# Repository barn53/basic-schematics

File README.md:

# basic-schematics

KiCAD dependencies:

https://github.com/gerdmuller/barn53-kicad-library.git

https://github.com/Digi-Key/digikey-kicad-library.git

KiCAD path:

```${BARN53_KICAD_DIR}```

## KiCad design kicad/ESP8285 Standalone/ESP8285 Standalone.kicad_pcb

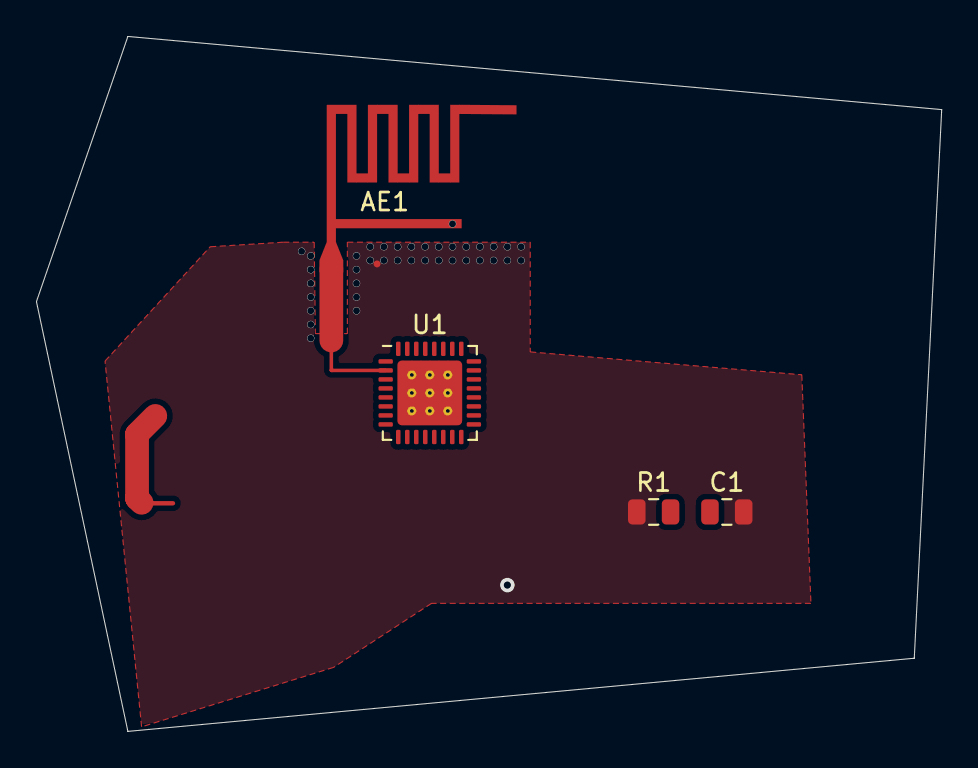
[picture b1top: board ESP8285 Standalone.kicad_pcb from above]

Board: 2 copper layers, 50.3 x 38.6 mm, 4 parts (0 on the bottom side), 2 nets.

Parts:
AE1: PCB_Antenna_2.4GHz_1mm; PCB_Antenna_2.4GHz_MIFA_Layout_1mm_FR4_PCB
C1: C; C_0805_2012Metric
R1: R; R_0805_2012Metric
U1: ESP_8285; QFN-32-1EP_5x5mm_P0.5mm_EP3.6x3.6mm_ThermalVias

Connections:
GND: AE1.2, C1.2, R1.1, U1.33
unnamed: AE1.1, U1.2

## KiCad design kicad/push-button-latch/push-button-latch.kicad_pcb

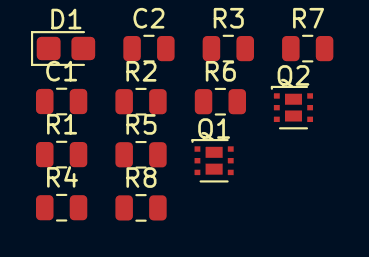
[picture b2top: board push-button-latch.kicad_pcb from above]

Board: 2 copper layers, 13 parts (0 on the bottom side), 10 nets, no tracks yet.

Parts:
C1: 330n; C_0805_2012Metric
C2: 100n; C_0805_2012Metric
D1: LED; LED_0805_2012Metric_Castellated
Q1, Q2: SIA527DJ-T1-GE3; PowerPAK_SC70-6L_Dual
R1, R8: 100k; R_0805_2012Metric
R2: 1M; R_0805_2012Metric
R3, R4, R5, R6: 10k; R_0805_2012Metric
R7: 470; R_0805_2012Metric

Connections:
GND: C1.2, C2.2, Q1.1, Q2.1, R4.2, R5.2
unnamed: C1.1, R2.2
unnamed: D1.1, R7.1
unnamed: Q1.3, R3.1, R4.1
unnamed: Q1.5, R1.1
unnamed: Q1.6, Q2.2, R3.2
unnamed: Q2.5, R8.1
unnamed: Q2.6, R1.2, R2.1, R6.2, R7.2, R8.2
Off: C2.1, Q1.2, R5.1
VCC: D1.2, Q1.4, Q2.4, R6.1

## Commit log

2019-11-16 first basic schematic: push button latch
2019-11-16 added: esp 12f minimal wiring
2019-11-17 added CP2104 USB UART Bridge
2019-11-19 added new schematics
2019-11-19 Used S8050 J3Y from barn53 library
2019-12-10 Added ESP 8285 Standalone
2020-01-07 Periodical commit
2020-01-07 Introduced the inverted notation
    e.g. ~RESET
2020-01-15 used parts
2020-02-04 saving commit
2020-10-07 minor
2020-10-27 additions
2021-05-03 Added CP2102 basic schematic
